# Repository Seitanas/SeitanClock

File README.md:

# SeitanClock
NTP clock based on ESP 12F (ESP8266)

## Features
- 7 segment RGB display. Also suports stock i2c LED displays with HT16K33 driver.
- Clock synchronization via NTP over Wi-Fi.
- Updates display intensity (and color) according to day and nigh time.
- Displays date and temperature.
- Easy to use configuration portal.
- Firmware update via Wi-Fi.

## Setup mode
Clock enters setup mode at first boot (when no Wi-Fi configuration is present yet).
To enter setup mode manually, power-cycle clock while pressing the button down.
Display will show `StP` message.
In setup mode clock acts as Wi-Fi hot-spot. There will be new Wi-Fi network `SeitanClock-setup` available. Connect to it with default password `seitanclock`. Point your browser to `http://seitanclock-setup.local`. 
<u>Note</u>, that Android phones seems to lack MDNS support, so in case you are using Android phone, point your browser to IP instead: `http://192.168.4.1`. Default username for portal is `admin`, password `admin`.
Use setup portal to configure your clock. Save and reboot after.

## Flash mode
Clock has a built-in feature to update its firmware via Wi-Fi.
To get latest firmware:
- Get latest code release from https://github.com/Seitanas/SeitanClock
- Open it with Arduino IDE.
- Enter clock setup portal via `http://seitanclock.local`
- Push `Enable flash mode` button. Clock should display `FLA` message.
- Go to Arduino IDE -> Tools -> Port. Select `SeitanClock-flash.local` (or if you have changed clock host name, use `YOURHOSTNAME-flash.local`). You may need to wait for a moment for network port to appear.
<u>Note</u>, that clock and computer you are running Arduino IDE must reside in the same network segment.
- Select Sketch -> Upload.
- Wait for upgrade to finish. Clock will restart automatically. Firmware upgrade leaves clock configuration intact.

## Component list
- 1m WS2812B DC5V, 144 IP30 RGB LED tape.
- 1pc DS3231 RTC module.
- 1pc GL5506 LDR photosensitive resistor.
- 1pc ESP-12f module.
- 1pc 1.2K 1206 SMD resistor.
- 5pcs 10K 1206 SMD resistor.
- 1pcs AMS1117 (LM1117) 3.3 voltage regulator. SOT-223 package.
- 2pcs 47uF 0605 SMD electrolytic capacitor.
- 3pcs 2.54 mm pitch MOLEX 1x2 connector.
- 1pc 2.54 mm pitch MOLEX 1x3 connector.
- 1pc 2.54 mm pitch MOLEX 1x4 connector.
- 1pc 2.54 mm 1x4 female header.
- 1pc 6x6mm Square tactile switch.
- 1pc USB-C [breakout board](https://www.adafruit.com/product/4396).

Electrical wiring diagram and PCB layout is done with CadSoft Eagle. You can find them in `eagle` folder.
Each display segment contains 3xWS2812B LEDs. Dots contain 1 WS2812B LED. Assemble segments in order as displayed in `img/segment_order.jpg` file.  
3D models can be found in `stl` folder. And also on:  
[Printables](https://www.printables.com/model/792393-seitanclock-rgb-ntp-clock)  
[Thingiverse](https://www.thingiverse.com/thing:6516316)

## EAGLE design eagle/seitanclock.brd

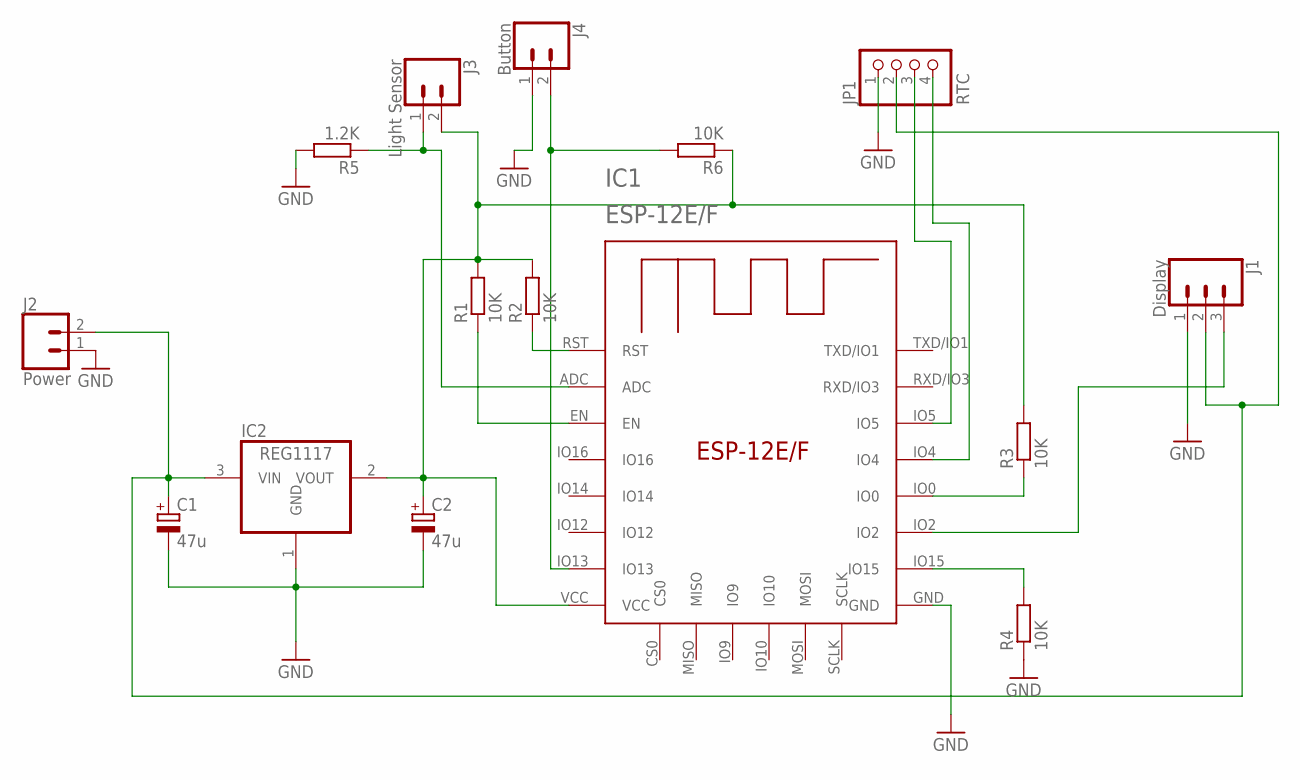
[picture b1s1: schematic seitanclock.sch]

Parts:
C1, C2: 47u; 153CLV-0605
IC1: ESP-12E/F; ESP-12E
IC2: REG1117; SOT223
J1: Display; MOLEX-1X3
J2: Power; MOLEX-1X2
J3: Light Sensor; MOLEX-1X2
J4: Button; MOLEX-1X2
JP1: RTC; 1X04
R1, R2, R3, R4, R6: 10K; R1206
R5: 1.2K; R1206

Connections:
GND: C1.-, C2.-, IC1.GND, IC2.1 (GND), J1.1, J2.1, J4.1, JP1.1, R4.1, R5.2
unnamed: IC1.IO5, JP1.3
unnamed: IC1.EN, R1.1
unnamed: IC1.RST, R2.1
unnamed: C2.+, IC1.VCC, IC2.2 (VOUT), J3.2, R1.2, R2.2, R3.2, R6.1
unnamed: IC1.IO15, R4.2
unnamed: IC1.IO0, R3.1
unnamed: IC1.IO4, JP1.4
unnamed: IC1.ADC, J3.1, R5.1
unnamed: IC1.IO2, J1.3
unnamed: IC1.IO13, J4.2, R6.2
unnamed: C1.+, IC2.3 (VIN), J1.2, J2.2, JP1.2

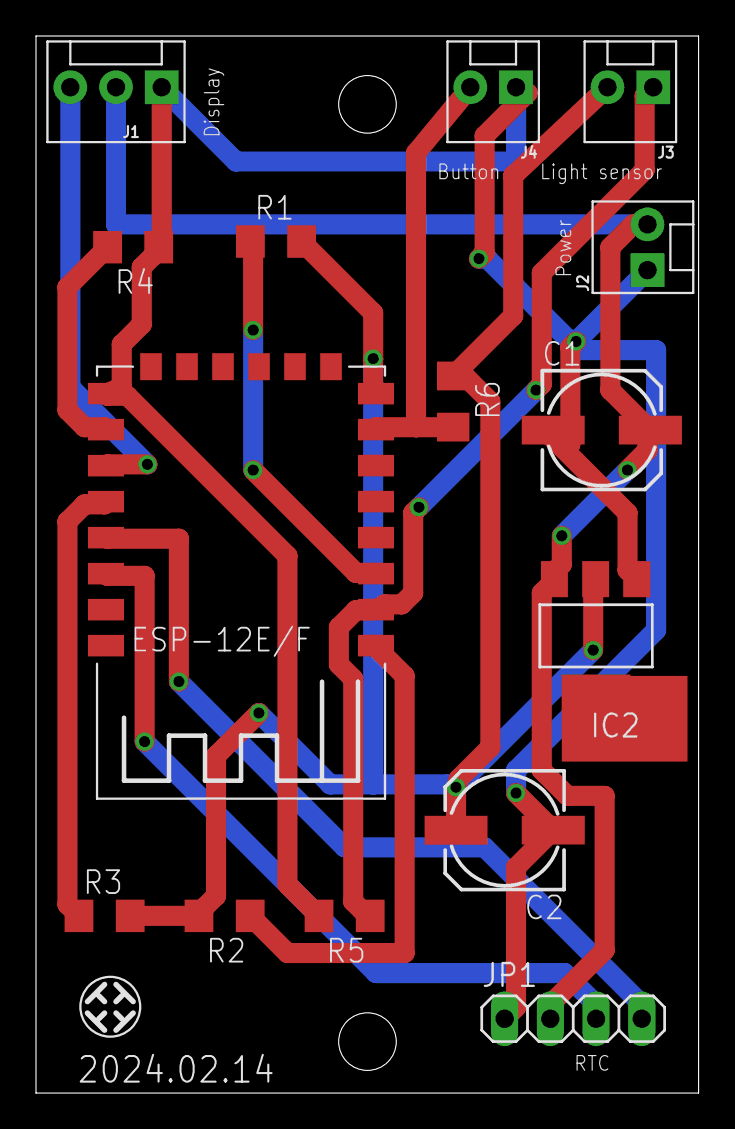
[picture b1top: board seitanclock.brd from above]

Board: 2 copper layers, 36.8 x 58.7 mm, 16 parts (0 on the bottom side), 12 nets.

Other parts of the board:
U$1: SEITAN_TNAME

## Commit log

2024-03-03 SeitanClock: initial release
2024-03-04 SeitanClock: add documentation
2024-03-04 SeitanClock: update readme
2024-03-04 SeitanClock: fix broken link
2024-03-04 SeitanClock: add 3D models
2024-03-04 SeitanClock: update formatting
2024-04-10 SeitanClock: adjust daylight savings via RTC
2024-05-01 SeitanClock: add HT16K33 display driver
2024-05-10 SeitanCLock: update RTC only on sucessfull NTP query
2024-05-13 SeitanClock: fix date formatting

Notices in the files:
parts and their libraries:
SparkFun-Connectors: Licensing: Creative Commons ShareAlike 4.0 International - https://creativecommons.org/licenses/by-sa/4.0
